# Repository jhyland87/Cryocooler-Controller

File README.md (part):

# ESP32-S3 Cryocooler Controller

Firmware for an ESP32-S3 DevKit that automates the cooldown sequence of a cryogenic cooler. The controller manages a compressor-driven cold stage through ten operational states — from a cold start at room temperature (~295 K) down to an operating setpoint of 78 K, with a graceful shutdown sequence — while enforcing thermal safety limits, detecting back-EMF current spikes, streaming live telemetry via Protobuf over WebSocket, and serving a real-time Preact dashboard over WiFi.

---

## Hardware

| Component | Part | Interface | Address / Pin | Purpose |
|-----------|------|-----------|---------------|---------|
| Microcontroller | ESP32-S3 DevKitC-1-N32R16V | — | — | Host MCU (32 MB flash, 16 MB PSRAM) |
| Cold-stage sensor | ADS1220 + PT1000 RTD | SPI mode 1 (main bus) | CS: decoder Y6 | Cold-stage temperature (4-wire, ratiometric) |
| Waveform generator | AD9837 DDS (AD9833 register set, 16 MHz clock) | SPI (main bus) | FSYNC (CS): decoder Y0 | 60 Hz sine wave for compressor |
| DAC | AD5453 14-bit multiplying | SPI mode 1 (main bus), write only | SYNC: decoder Y1 | Amplifier amplitude control |
| Power monitor | INA239 + 10 mΩ shunt | SPI mode 1 (main bus) | CS: decoder Y2, ALERT: expander GP6 | 12 V rail voltage, current and power |
| IMU | LSM6DSOX on the cryocooler: its own 18 x 18 mm board (`hardware/kicad/imu/`, not yet built) or the Adafruit breakout it replaces | SPI (main bus) via header J14 | CS: decoder Y7, INT1: GPIO 2, INT2: GPIO 39 | Vibration / overstroke detection |
| Fan / pump | 4-pin PWM through a BSS138DW dual driver | LEDC PWM + PCNT tach | PWM: GPIO 9 / 14, tach: GPIO 15 / 21 | Cooling fan + pump |
| Current sensor | ACS37800-015B5 (±15 A) behind an ISOW7741 isolator | SPI mode 3 (main bus, through two gates) | CS: decoder Y5 (rev 5; GPIO 17 on rev 4) | Amplifier AC current monitoring |
| Compressor relay | BSS138 → BSS84 high-side +12 V switch (130 mA max) | GPIO | GPIO 16 | Compressor relay on/off |
| Amplifier relay | BSS138 → BSS84 high-side switch | GPIO | GPIO 6 | Amplifier REM line on/off |
| Coolant flow sensor | Alphacool ES (Hall-effect) | GPIO | GPIO 18 | Coolant flow pulses |
| Coolant temperature | NTC thermistor | ADC | GPIO 4 | Coolant temp via voltage divider |
| Status LED | WS2812B-2020 RGB | GPIO | GPIO 38 | Fault / Ready indication |
| Expander | MCP23S08 | SPI (main bus) | CS: decoder Y3 | ±15 V flags, INA239 ALERT, ADT7320 INT and CT, 3 spare pins (rev 5; rev 4 also has the display backlight and touch IRQ) |
| Display (rev 5, schematic only) | Waveshare ESP32-S3-Touch-LCD-4.3B, off-board, with its own ESP32-S3 and firmware | CAN through a TCAN3414 (rev 6: one 6-pin JST PH header J15 inside the board, which also feeds it fused, unswitched 12 V) | CAN TX: GPIO 17, RX: GPIO 12 | Shows telemetry and sends commands. Its two digital outputs press the power button and RESET through J15 pins 5 and 6 (rev 5: header J21). Rev 6.1 adds J42 (JST PH: CAN_L, CAN_H, GND) to carry the bus on, and a 0 Ω link JP20 to take out the 120 Ω terminator when this board is mid-bus. No CAN firmware yet (the firmware still drives the rev 4 ST7789V + TSC2046) |
| Ambient temperature (rev 5, schematic only) | ADT7320 | SPI mode 3 (main bus) | CS: decoder Y8, INT / CT: expander GP2 / GP3 | Ambient temperature; replaces the reading the I2C fan controller gave |
| Power button | LTC2954 INT# / KILL# | GPIO | GPIO 1 / GPIO 10 | Button press ramps down, then cuts system power |
| General-purpose I/O | 2-pin headers J16-J18 and J20 (rev 4 also has J19 on GPIO 12) (signal, GND), each with an LED that follows the pin voltage | GPIO; ADC on IO5 / IO7 only | GPIO 5, 7, 11, 13 | Spare 3.3 V inputs or outputs (sensors, relay triggers, LEDs) |
| AUX header (rev 6) | 5-pin JST PH header J40 inside the board: 5 V, 3.3 V, GPIO11, GPIO13, GND; 100 Ω and an ESD clamp per line, pull-up footprints not fitted. Rev 6.1 adds a Qwiic / STEMMA QT header J41 on the same lines (1 GND, 2 3.3 V, 3 SDA = GPIO11, 4 SCL = GPIO13) | UART, I2C, 1-Wire, touch (T11, T13) or GPIO, chosen in firmware; ADC2 only with WiFi off | GPIO 11, 13 | Spare port for a later add-on. No firmware uses it yet |

**I2C:** none. Every peripheral is on SPI or a GPIO.

**Main SPI bus:** CLK → GPIO 42, MOSI → GPIO 41, MISO → GPIO 40. Devices: AD9837, AD5453, the LSM6DSOX (on a cable, header J14), INA239, ADS1220, MCP23S08, the ACS37800 and, up to rev 4, the display and its TSC2046 touch controller. Their chip selects come from the 74HC154 4-to-16 decoder (rev 5; rev 4 has an SN74LVC138A with eight outputs), driven from GPIO 3, 44, 45, 47 (through a 74LV1T34 buffer, because it is 1.8 V) and 8, with Y4 (rev 5) and Y9 to Y15 spare. The INA239, ADS1220 and AD5453 use SPI mode 1, and the INA239 and ADS1220 data outputs are high-impedance while CS is high. The ADS1220 DRDY pin is not wired to the MCU.

**ACS37800:** on the main SPI bus, with CS on GPIO 17 (a plain GPIO, not a decoder output) on rev 4, and on decoder output Y5 in the rev 5 schematic. The ACS37800 keeps MISO driven when CS is high, so two SN74LVC1G125 gates connect it only while CS is low: one passes SCK to the isolator, the other passes its MISO to the bus. See [`docs/acs37800.md`](docs/acs37800.md) for its SPI frame and bring-up gotchas.

**General-purpose I/O:** each of the five pins has 100 Ω in series, 200 kΩ to ground (the LED driver's divider) and an ESD clamp, and is 3.3 V only. GPIO 5 and 7 are ADC1 and can read analog with WiFi on; GPIO 11-13 are ADC2, so digital only. The firmware defines the pins (`AUX_IO*_PIN`) but does not use them yet.

**Fan and pump:** each PWM GPIO drives a BSS138 (GPIO high = PWM line low = 0 % drive), because the fan PWM line can reach 5.25 V. A 10 kΩ gate pull-up holds 0 % drive during boot. Each tach line has a 4.7 kΩ series resistor, a clamp on the GPIO side, and a 4.7 kΩ pull-up to 3.3 V. The 12 V pin of each header is fed through its own Bourns resettable fuse (F3 fan: MF-MSMF050/24X, 0.5 A hold; F4 pump: MF-MSMF250/16X, 2.5 A hold; nets `+12V_FAN`, `+12V_PUMP`), so a shorted cable trips it instead of F1. The parts are on the schematic and on the rev 7 board.

**INA239 ALERT:** drives its red LED only; it is not wired to the MCU, and the firmware does not read it.

### Circuit board

The 4-layer board (rev 7: 170 x 120 mm, for the Phoenix UCS 195-145 housing, routed, not bench tested; see [`hardware/HANDOFF_rev7.md`](hardware/HANDOFF_rev7.md)) is routed from the KiCad schematic in [`hardware/kicad/`](hardware/kicad/README.md). It has no section boxes on the silkscreen.

### System wiring

Every off-board connection except the GPIO headers J16 to J20. The order of the parts in the coolant loop is assumed. Redraw it with `python3 hardware/kicad/tools/gen_wiring_diagram.py`.

---

## Architecture

All subsystem modules follow a standardised lifecycle pattern built on a CRTP base class (`ModuleBase<T>`) with compile-time interface enforcement. Modules are registered in declarative arrays and initialised/serviced via generic helpers — adding a new module is a one-liner. See [`docs/modules.md`](docs/modules.md) for the full module authoring guide.

```mermaid
flowchart TD
    subgraph Persistent ["Persistent Modules (init once at startup)"]
        HW[hardware<br/>SPI buses]
        IMU[imu<br/>LSM6DSOX accelerometer]
        CMD[commands<br/>Serial console]
        DASH[dashboard<br/>WiFi + Preact SPA + WebSocket]
        TEL[telemetry<br/>Protobuf frame builder]
        SYS[sysinfo<br/>INA239 power monitor]
        OTA[ota<br/>HTTP firmware updates]
    end

    subgraph Control ["Control Modules (re-init on every Initialize state)"]
        COOL[cooling<br/>PWM fan + pump<br/>software LUT]
        CH[cold_head<br/>ADS1220 PT1000 RTD]
        AMP[amplifier<br/>AD9837 + AD5453 DAC + ACS37800]
        COMP[compressor<br/>relay GPIO]
        IND[indicator<br/>WS2812 RGB LED]
    end

    subgraph FSM ["Core Logic"]
        SM[state_machine<br/>Pure FSM — no hardware calls]
    end

    CH  -->|tempC, coolingRate, stalled| SM
    AMP -->|rmsV, overstroke| SM
    IMU -->|overstroke| SM
    SYS -->|sysVoltage| SM

    SM -->|dacTarget| AMP
    SM -->|compressorRelay, amplifierRelay| COMP
    SM -->|faultIndMode, readyIndMode| IND
    SM -->|Output| TEL

    TEL --> DASH
    TEL --> CMD

    classDef persistent fill:#dbeafe,stroke:#3b82f6,color:#1e3a5f
    classDef control    fill:#dcfce7,stroke:#16a34a,color:#14532d
    classDef fsm        fill:#fef3c7,stroke:#d97706,color:#78350f

    class HW,IMU,CMD,DASH,TEL,SYS,OTA persistent
    class COOL,CH,AMP,COMP,IND control
    class SM fsm

    style Persistent fill:#eff6ff,stroke:#93c5fd
    style Control    fill:#f0fdf4,stroke:#86efac
    style FSM        fill:#fffbeb,stroke:#fcd34d
```

---

## Module Reference

### hardware

Initialises the main SPI bus (`SPI.begin(...)`), which the ACS37800 shares.

---

### state_machine

The core of the controller. Ingests sensor readings every tick and outputs a complete set of actuator targets. Contains no hardware calls — pure logic, fully unit-testable on the host PC.

**States:**

| # | Name | Description | FAULT LED | READY LED | DAC |
|---|------|-------------|-----------|-----------|-----|
| -1 | Off | System powered down | Off | Off | 0 |
| 0 | Initialize | Power-up self-check | Solid Amber | Solid Amber | 0 |
| 1 | Idle | Warm standby | Solid Red | Off | 0 |
| 2 | CoarseCooldown | Cooling above 85 K | Flash Fast Red | Off | proportional to temp |
| 3 | FineCooldown | Cooling below 85 K | Flash Fast Red | Flash Slow Green | proportional to temp |
| 4 | Overshoot | Below setpoint, settling | Flash Fast Red | Flash Fast Green | 0 |
| 5 | Settle | In setpoint band; Normal relay | Flash Fast Red | Flash Fast Green | 0 |
| 6 | Baseline | Collecting pre-run baseline (5 min) | Off | Solid Green | 0 |
| 7 | Operating | Normal cryogenic operation | Off | Solid Green | 0 |
| 8 | Shutdown | Graceful shutdown; DAC ramps down | Off | Off | ramps → 0 |
| 9 | Delay | Timed hold; resumes at configured next state | Solid Amber | Solid Amber | 0 |
| 127 | Fault | Terminal fault state | Flash Fast Red | Off | 0 |

**Key configuration** (all in `config.h`):

| Constant | Default | Description |
|----------|---------|-------------|
| `SETPOINT_C` | -195.15 °C (78 K) | Target cold-stage temperature |
| `COARSE_FINE_THRESHOLD_C` | -188.15 °C (85 K) | Coarse/Fine transition boundary |
| `SETPOINT_TOLERANCE_C` | 3.0 °C | Band around setpoint for settle/overshoot logic |
| `SETTLE_DURATION_MS` | 60 000 ms | Time stable before advancing to Baseline |
| `BASELINE_DURATION_MS` | 300 000 ms | Baseline collection window |
| `SHUTDOWN_DURATION_MS` | 5 000 ms | Graceful shutdown ramp duration |
| `STALL_DETECT_WINDOW_MS` | 600 000 ms | Stall detection observation window |
| `STALL_MIN_DROP_C` | 2.0 °C | Minimum temp drop required in the window |
| `BACKOFF_MAX_COUNT` | 10 | Max overstroke events before TooManyBackoffs fault |

---

### cold_head

Reads the PT1000 RTD via the ADS1220 24-bit ADC over SPI (mode 1, chip select GPIO 44). The ADC is configured for 4-wire ratiometric measurement (gain 1, PGA bypassed, 20 SPS with simultaneous 50/60 Hz rejection) with 250 µA IDAC excitation and a 3854 Ω external reference resistor. Raw ADC counts are converted to resistance, then to temperature via the Callendar-Van Dusen equation (above 0 °C) and AN709 polynomial (below 0 °C).

Uses a non-blocking two-phase state machine: start single-shot conversion → wait out the 50 ms conversion time (DRDY is not wired) → read the 24-bit result. Maintains a ring buffer of `TEMP_HISTORY_SIZE` timestamped samples for cooling-rate calculation (°C/min), stall detection, and cooldown progress (0–100 %).

The temperature is reported (telemetry, dashboard, run history, display) only once it has settled: `COLD_HEAD_STABLE_READINGS` consecutive readings, each within `COLD_HEAD_STABLE_BAND_C` of the one before (about 2 s after boot, and again after any sensor fault). Until then it is sent as "no reading" instead of 0. This gate is for reporting only; the state machine's sensor-fault check is unchanged.

| Function | Returns |
|----------|---------|
| `getLastTempK()` | Cold-stage temperature in Kelvin |
| `getLastTempC()` | Cold-stage temperature in Celsius |
| `getCoolingRateCPerMin()` | °C/min, positive = cooling |
| `isStalled()` | True if stall threshold exceeded |

---

### amplifier

Drives the AD9837 DDS (60 Hz sine wave, through the MD_AD9833 library set to a 16 MHz clock), the AD5453 14-bit multiplying SPI DAC (amplifier amplitude), the amplifier relay (GPIO 6) and the ACS37800 current sensor. Provides two ramp modes:

- `rampToVoltage(target)` — smooth ramp at ±`DAC_MAX_STEP_PER_INTERVAL` per tick
- `rampTowardShutdown(target)` — fast ramp at ±`DAC_SHUTDOWN_STEP_PER_INTERVAL` per tick

**Overstroke (back-EMF) detection:** A slow-tracking EMA forms the baseline. A reading exceeding `baseline + OVERSTROKE_CURRENT_THRESHOLD_A` fires `hasOverstroke()`, subject to `OVERSTROKE_DEBOUNCE_MS`. The EMA is primed for `OVERSTROKE_PRIME_READINGS` ticks on startup.

---

### imu

Drives the LSM6DSOX 6-DOF IMU over SPI (CS GPIO 1) in FIFO mode at 833 Hz. The sensor is mounted on the cryocooler, so it sees the cooler body's vibration. It is cabled to header J14: the IMU board (`hardware/kicad/imu/`, not yet built) or, until then, the Adafruit breakout (product 4438); pinouts are in `hardware/kicad/README.md`. The SPI clock is `LSM6DSOX_SPI_FREQUENCY_HZ`. A missing cable is non-fatal: the module reports unavailable. On `init()` the module sets `I2C_disable` in CTRL4_C (13h) right after the driver's `begin_SPI()`, so the IMU's I²C block ignores traffic for the other devices on the shared SCK/MOSI lines (DS12814 §5.1.1; the driver only disables I3C). The sensor is then configured and a one-time blocking calibration collects samples to compute per-axis offsets (gravity is removed from the Z offset).

Each `service()` call applies calibration offsets, runs a first-order low-pass filter, and computes roll/pitch from filtered acceleration. Motion / overstroke is flagged when acceleration magnitude deviates from 9.81 m/s² by more than `ACCEL_THRESHOLD_MPS2`; it clears after `MOTION_TIMEOUT_MS` of stillness.

A periodic FFT (`calculateFrequency()`) detects the compressor vibration frequency in the 45–75 Hz band using 256 samples at 833 Hz, with Hann windowing and quadratic peak interpolation.

| Function | Returns |
|----------|---------|
| `isInitialized()` | True if sensor was found and configured |
| `hasOverstroke()` | True while motion/overstroke is active |
| `getRoll()` / `getPitch()` | Orientation angles in degrees |
| `getAccelMag()` | Calibrated acceleration magnitude (m/s²) |
| `getFrequencyHz()` | Detected compressor frequency (Hz), or NAN |
| `getTemperature()` | IMU die temperature (°C); mounted on the cooler, this is the cooler-body temperature and also feeds the "ambient" value |

---

### sysinfo

Reads the 12 V rail voltage, current and power from the INA239 power monitor over SPI (10 mΩ shunt, 10 A calibration; GPIO 3 chip select) and exposes `getVoltage()`, `getCurrent()` and `getPower()`. SPI has no ACK, so each tick first reads the INA239 manufacturer and device ID registers; after 3 consecutive failures (for example when 12 V drops) the module disables itself until `reinit`. It also tracks CPU load, heap and PSRAM.

---

### cooling

Controls the cooling fan and pump directly from the ESP32: LEDC generates 25 kHz PWM and PCNT counts the tach pulses. Also samples the Alphacool ES flow sensor and NTC coolant temperature.

**Software LUT:** Each channel has an independently-configured temperature-to-duty lookup table with hysteresis, evaluated once per second from coolant temperature. Entries are sorted ascending by temperature; the evaluator only writes to the chip when the active row changes.

**Fault detection:** A channel with drive applied and no tach pulses for `COOLING_TACH_STALL_MS` raises `hasFanFault()`. It is reported in telemetry and logs and does not fault the state machine.

**Pump normalisation:** User-facing pump speeds are 0–100 % normalised, mapped to 0–`COOLING_PUMP_MAX_DUTY_PCT` (raw 0–255) at the hardware boundary. The pump stalls above ~16 % effective duty (~4400 RPM).

**Tracking monitors:** Score-based monitors for fan duty, coolant temperature, and flow rate detect sustained deviations from expected values.

| Function | Returns |
|----------|---------|
| `getCoolantTemperature()` | Coolant temperature in °C |
| `getCoolantFlowRate()` | Coolant flow rate in L/min |
| `getFanSpeed()` | Fan duty (0–255) |
| `getFanRPM()` | Fan tachometer RPM |
| `getPumpSpeed()` | Pump speed (normalised 0–100 %) |
| `getPumpRPM()` | Pump tachometer RPM |
| `hasFanFault()` | True while a driven channel has no tach pulses |
| `getFanFaultDurationMs()` | Duration of current fault episode |

---

### compressor

Manages the compressor relay (GPIO 16 → high-side +12 V switch) with timed-run support. `compressor start <duration>` energises the relay for a specified duration (e.g. `1h30m`, `45s`), clamped to `COMPRESSOR_MAX_RUN_MS`. Can be disabled at compile time with `ENABLE_COMPRESSOR false`.

---

### indicator

Drives the on-board WS2812 RGB LED (GPIO 38) according to the state machine's requested `Mode`. All flash timing is non-blocking — `update(nowMs)` is called every loop iteration.

| Mode | Colour | Rate |
|------|--------|------|
| `SolidRed` | Red | — |
| `SolidGreen` | Green | — |
| `SolidAmber` | Amber | — |
| `FlashFastRed` | Red | 2 Hz |
| `FlashSlowGreen` | Green | 1 Hz |
| `FlashFastGreen` | Green | 2 Hz |

---

### dashboard

Connects to WiFi and serves a Preact single-page application with real-time telemetry:

- **HTTP** (port 80): serves the embedded SPA (`index.html`, `app.js`, `style.css`) and a JSON telemetry endpoint at `GET /api/telemetry`
- **WebSocket** (`ws://<hostname>/ws` on port 80): streams Protobuf-encoded telemetry frames at 1 Hz
- **Network panel**: hostname, IP address, joined WiFi network and signal strength, from the `network.*` telemetry group
- **mDNS**: `cryocooler.local` by default. Change `HOSTNAME` in `include/config/config.h`; the firmware and the dashboard build both read it, so rebuild both (a full `pio run`).

The dashboard frontend uses Preact + MUI + Vite and is bundled into firmware flash at build time via `scripts/embed_web.py`. WiFi credentials are set from the serial console (`wifi set`) and saved in NVS flash; see [WiFi credentials](#wifi-credentials).

---

### ota

HTTP OTA firmware update endpoint. `GET /ota` serves an upload form; `POST /ota` flashes new firmware. Enabled with `ENABLE_OTA true` in `config.h`. Every `/ota` request needs the OTA login; see [Passwords](#passwords).

---

### commands

Non-blocking USB serial command handler. `service()` accumulates characters and dispatches completed lines. The same `processLine()` function is used by the TCP server and by unit tests with a stub `Print`.

| Command | Action |
|---------|--------|
| `start` | Begin cooldown (from Off or Idle) |
| `stop` | Abort and return to Idle |
| `off` | Power off the system entirely |
| `reboot` | Reboot the MCU |
| `status` | Print current state and running flag |
| `summary` | Full snapshot of all sensor and actuator values |
| `fsm state` | Print current FSM state with time-in-state |
| `fsm history` | Print recent FSM state transitions |
| `fault clear` | Clear an active fault and return to Idle |
| `fault push` | Push a fault record |
| `fault history` | Print fault log with reason and clear method |
| `board` | Print compile-time board/platform info |
| `reinit` | Re-initialise all or named modules |
| `wifi status` | Print WiFi on/off state, saved settings, link, signal, TX power and last disconnect reason |
| `wifi retry` | Start a new WiFi connection attempt now |
| `wifi on` / `wifi off` | Turn WiFi on or off until reboot |
| `wifi onboot <on\|off>` | Save whether WiFi starts at boot (also `true`/`false`/`1`/`0`); no argument prints the setting |
| `wifi scan` | List visible networks with RSSI, channel and security (serial port only) |
| `wifi set <ssid>` | Save a network; the passphrase is asked for on the next line |
| `wifi forget` | Erase the saved network and disconnect |
| `dashboard password` | Set or remove the dashboard password; asked for on the next line (`none` removes it) |
| `ota password` | Set the OTA update password; asked for on the next line (`default` restores the default) |
| `dashboard logout` | End every dashboard login, including remembered ones |
| `password status` | Show whether each password is set (never prints them) |
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
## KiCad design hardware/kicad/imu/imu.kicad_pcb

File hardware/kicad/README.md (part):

# Cryocooler controller — KiCad schematic

KiCad 10 hierarchical schematic for the ESP32-S3 cryocooler controller. Open
`cryocooler.kicad_pro`. A PDF export is in `cryocooler-schematic.pdf`. The 4-layer board is `cryocooler.kicad_pcb` (see [PCB layout](#pcb-layout)).

GPIO assignments follow [`include/config/pin_config.h`](../../include/config/pin_config.h).
The top-level README hardware table was brought in line with these sheets and the firmware
on 2026-10-14; if the two ever disagree, the schematic and `pin_config.h` win.

## Sheets

| Sheet | Contents |
|---|---|
| `cryocooler.kicad_sch` (root) | ESP32-S3-WROOM-2-N32R16V, EN/BOOT, USB-C (GCT USB4205-GF-A, flag type) + ESD |
| `power_input` | 12 V DC jack (5.5 x 2.1 mm), 5 A fuse, SMBJ16A TVS, bulk caps Rev 5 (2026-11-16): sized for 10 A. J2 is a Molex Mini-Fit Jr 2 x 2 pinned as the ATX 12 V (CPU) connector (1, 2 ground; 3, 4 +12 V) and F1 is 10 A. |
| `power_button` | LTC2954CDDB-2 (INT# to GPIO1), AONR21307 high-side P-FET with slow-start gate network and 15 V clamp, KILL# bias, red standby LED through 13 kΩ and one BSS138, TPD1E05U06 on the button line `PWR_BTN` (the J7 panel header went in rev 4). Rev 5: `PWR_BTN` is a global label, so the display's digital output on the `display` sheet (J21) presses the same line as SW3 Rev 5: optional auto power-on (JP, 2.2 µF and a diode on `PWR_BTN`), jumper not fitted, not bench tested. |
| `rails_logic` | AP63205 buck with SRP4020TA-4R7M (12→5 V); TPS2116 selects +5V or USB VBUS into +5V_OR, priority to the 12 V side → TPS62822 buck with SRP4020TA-R47M (→3.3 V) |
| `rails_15v` | ADP5071ACPZ dual converter at 1.2 MHz with SRP7050TA-3R3M and -6R8M (rev 1 values) → one LT3097 dual LDO (±14.7 V, 147 kΩ SET resistors); the LT3097 PGP / PGN go to the `power_good` sheet Rev 5 (2026-11-16): the LT3097 (no stock) is replaced by an LT3045 (MSOP-12, U21) and an LT3094 (DFN-12, U22) with the same SET, PGFB and output parts. |
| `ldo_15v` ("Regulators +-15V") | The LT3045 (+15 V) and LT3094 (-15 V) post-regulators with their SET, PGFB and output parts. Split off `rails_15v` in the schematic redraw (that sheet was over 30 parts); the circuit and the references are unchanged. Its block carries the PGP_15V / PGN_15V pins. |
| `power_good` | One node and green LED per LT3097 PG pin (with a 470 k / 470 k guard and BSS138W so a missing -15 V pulls `PGN_15V` low), a BAT54AW AND of the two nodes into `PG_15V`, and the 3.3 V flag `PG_15V_N` on GPIO43 (low = both ±15 V rails good); both flags are also read by the MCP23S08 |
| `signal_gen` | ECS-2520MV 16 MHz oscillator, AD9837 (LFCSP-10), OPA2991 dual U5 (A: gain 16.3; B: AD5453 output stage, 22 pF C1), R39 + MMBZ9V1 clamp into AD5453 VREF, AD5453 (decoder Y1); all digital parts on `+3V3_SG` |
| `amp_control` | GPIO6 → BSS138 → BSS84 high-side 12 V to amplifier REM, red/green LED; a second BSS138 (Q9) in series with the level shifter's source is gated by `PG_15V`, so REM cannot turn on unless both ±15 V rails are good |
| `amp_current` | ACS37800-015B5 (SPI, ±15 A at 5 V) + ISOW7741 (isolated 5 V and SPI in one part) with FB1 / FB2, 4×1 MΩ + 4.02 kΩ divider, TE 2305908-2 SMT pluggable header J11, TE 643228-1 through-hole header J12. Rev 4: on the shared SPI bus through two SN74LVC1G125 gates enabled by `ACS_CS` (U41 passes SCK in, U42 passes MISO out), with 10 kΩ pull-ups on the gated SCK and on `ACS_CS` Rev 5 (2026-11-15): the ISOW7741 (no stock) is replaced by an ISOW7841AQDWERQ1 on `+3V3_ISO` (40 mA at 5 V out); FB1 / FB2 and the EN/FLT pull-up are gone. |
| `system_current` | INA239 (SPI mode 1, decoder Y2) + 15 mΩ shunt in the switched 12 V rail, 49.9 Ω / 470 nF input filter, ALERT to expander GP6, ALERT and 3V3 power LEDs Rev 5: the shunt is a 4-terminal part whose sense pads feed the filter, and VBUS sits on `+12V` directly. Later (2026-11-16): the shunt is a 10 mΩ Vishay WSK2512 (16.4 A full scale). |
| `gpio_expander` ("GPIO Expander") | MCP23S08 QFN-20 on the shared SPI bus (mode 0, decoder Y3), on unswitched `+3V3`: GP0-1 power-good flags, GP6 INA239 ALERT, GP2/GP3 ADT7320 INT/CT, GP4, GP5 and GP7 spare (rev 5; GP4 was the display backlight enable and GP7 the touch IRQ); RESET tied to +3V3, A0/A1 and exposed pad to GND, INT to a test point Rev 5 universal I/O: GP4 is `IO_EXP_INT_N` and GP5 `IO_ADC_DRDY_N`; only GP7 is spare. |
| `cooling` ("Water Cooling") | Fan and pump: LEDC PWM through the two halves of one BSS138DW (Q61) as open-drain drivers (gates held on by 10 kΩ to `+3V3`, so 0% drive at reset), tach through 4.7 kΩ to PCNT; Alphacool ES flow tach and NTC; connector-side pull-ups sit on the switched `+3V3_COOL` rail. 2026-11-23: the +12 V pin of J3 and J4 is fed through resettable fuses F3 (MF-MSMF050/24X, net `+12V_FAN`) and F4 (MF-MSMF250/16X, net `+12V_PUMP`), each with its 22 uF cap on the header side; on the rev 7 board both stand on the back above J4, with the pump fuse's pad 1 straight to J4 pin 2 and the fan fuse's through two vias to J3 pin 2. Rev 4: XKB X2510WRS headers (J5 is a 4-pin part with pin 4 unused), 4.7 kΩ and 10 kΩ resistors in arrays RN1 / RN2 |
| `cold_head` ("Cold Head Temp") | ADS1220 (SPI mode 1, CS on GPIO44), 4-wire PT1000, 3.9 kΩ Rref, DRDY pull-up + test point; powered from the switched `+3V3_CH` rail |
| `imu` | J14, a Molex Micro-Lock Plus 2x4 header (505448-0891, 1.25 mm, right angle, positive lock) for the off-board Adafruit LSM6DSOX module: SPI bus, CS, INT1/INT2, +3V3, GND; one NUF6401MN six-channel filter (100 Ω series, 17 pF and ESD clamp each side) |
| `compressor_relay` | GPIO16 → BSS138 → BSS84 high-side +12 V switch, flyback diode, red/green state LED, 2-pin right-angle XKB X2510WRS-02 output |
| `indicators` | WS2812B-2020 status LED behind a 74AHCT1G125 level shifter |
| `debug` | Test points on rails, grounds and control lines; LEDs on +5V and ISO 5V |
| `supply_switches` | 5 Keystone 5110 0603 zero-ohm jumpers JP1-JP5, one per section, in series with that section's supply (see "Supply jumpers" below); FB3 ahead of JP5 Rev 5: JP3 now feeds `+3V3_ISO`, and JP6 with FB4 feeds `+5V_IO` from `+5V` (universal I/O ADC, range switches and sensor excitation). |
| `display` | Rev 5: link to the off-board Waveshare ESP32-S3-Touch-LCD-4.3B, which runs its own firmware. TCAN3414 CAN transceiver (U52, `CAN_TX` GPIO17 with a 10 kΩ pull-up, `CAN_RX` GPIO12, 120 Ω termination R516) to J15 (X2510WRS-04: 1 GND, 2 unswitched 12 V `VIN`, 3 CAN_H, 4 CAN_L). J21 (X2510WRS-04: 1 GND, 2 power button, 3 reset, 4 unused) lets the display's two open-collector outputs press the global `PWR_BTN` like SW3 and pull `ESP_EN` low like the RESET button, each through 100 Ω with a TPD1E05U06 clamp. Rev 4 and earlier: FH12-14S FPC to the Phoenix 2.4" ST7789V display with a TSC2046 touch controller Later on 2026-11-15: J15 and J21 became one 6-pin connector J15 (1 GND, 2 fused 12 V, 3 CAN_H, 4 CAN_L, 5 power button, 6 reset), with a 0.5 A resettable fuse F2 and an ESD2CAN24 clamp; since 2026-11-16 the cable ends in two XKB headers back to back, as XKB makes no 6-pin part: J15 (X2510WRS-04: 1 CAN_H, 2 CAN_L, 3 power button, 4 reset) and J21 (X2510WRS-02: 1 GND, 2 fused 12 V). Rev 6 (2026-11-18): one 6-pin top-entry JST PH header J15 again (B6B-PH-SM4-TB: 1 GND, 2 fused 12 V, 3 CAN_H, 4 CAN_L, 5 power button, 6 reset); J21 is gone. |
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
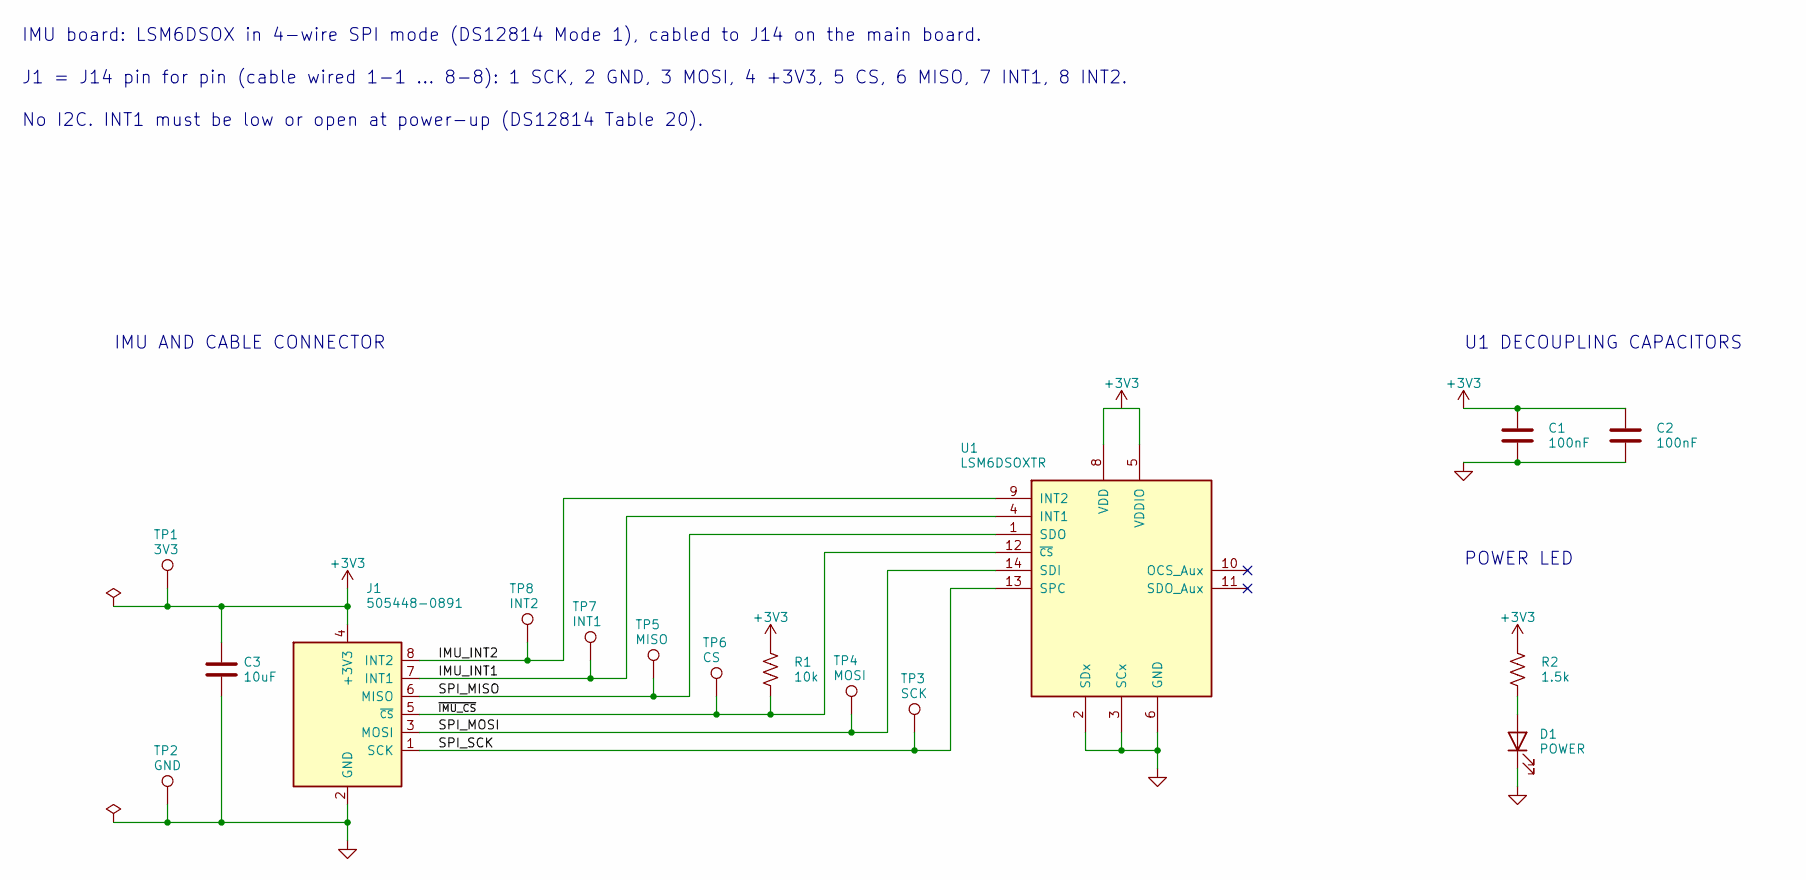
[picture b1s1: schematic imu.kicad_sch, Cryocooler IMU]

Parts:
C1, C2: 100nF; C_0402_1005Metric
C3: 10uF; C_0805_2012Metric
D1: POWER; LED_0402_1005Metric
J1: 505448-0891; Molex_Micro-Lock_Plus_505448-0891_2x04_P1.25mm_Horizontal
R1: 10k; R_0402_1005Metric
R2: 1.5k; R_0402_1005Metric
TP1: 3V3; TestPoint_Pad_D1.0mm
TP2: GND; TestPoint_Pad_D1.0mm
TP3: SCK; TestPoint_Pad_D1.0mm
TP4: MOSI; TestPoint_Pad_D1.0mm
TP5: MISO; TestPoint_Pad_D1.0mm
TP6: CS; TestPoint_Pad_D1.0mm
TP7: INT1; TestPoint_Pad_D1.0mm
TP8: INT2; TestPoint_Pad_D1.0mm
U1: LSM6DSOXTR; LGA-14_3x2.5mm_P0.5mm_LayoutBorder3x4y

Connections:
+3V3: C1.1, C2.1, C3.1, J1.4 (+3V3), R1.1, R2.1, TP1.1, U1.5 (VDDIO), U1.8 (VDD)
/IMU_INT1: J1.7 (INT1), TP7.1, U1.4 (INT1)
/IMU_INT2: J1.8 (INT2), TP8.1, U1.9 (INT2)
/SPI_MISO: J1.6 (MISO), TP5.1, U1.1 (SDO)
/SPI_MOSI: J1.3 (MOSI), TP4.1, U1.14 (SDI)
/SPI_SCK: J1.1 (SCK), TP3.1, U1.13 (SPC)
/~IMU_CS: J1.5 (~CS), R1.2, TP6.1, U1.12 (~CS)
GND: C1.2, C2.2, C3.2, D1.1 (K), J1.2 (GND), TP2.1, U1.2 (SDx), U1.3 (SCx), U1.6 (GND), U1.7 (GND)
unnamed: D1.2 (A), R2.2

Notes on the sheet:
U1 DECOUPLING CAPACITORS
J1 = J14 pin for pin (cable wired 1-1 ... 8-8): 1 SCK, 2 GND, 3 MOSI, 4 +3V3, 5 CS, 6 MISO, 7 INT1, 8 INT2.
IMU AND CABLE CONNECTOR
No I2C. INT1 must be low or open at power-up (DS12814 Table 20).
POWER LED
IMU board: LSM6DSOX in 4-wire SPI mode (DS12814 Mode 1), cabled to J14 on the main board.

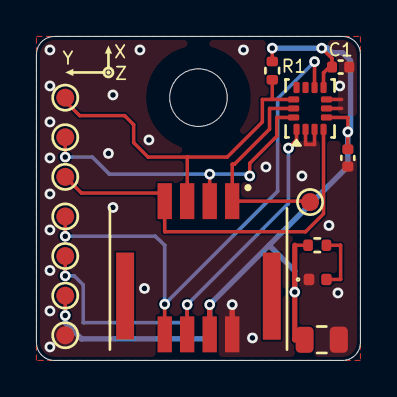
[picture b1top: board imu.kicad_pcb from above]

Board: 2 copper layers, 18.0 x 18.0 mm, 16 parts (0 on the bottom side), 9 nets.

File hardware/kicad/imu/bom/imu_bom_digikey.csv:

Quantity,Manufacturer Part Number,Manufacturer,Description,Customer Reference,Value,Package,MPN basis,Notes
2,CL05B104KB54PNC,Samsung Electro-Mechanics,CAP CER 0.1UF 50V X7R 0402,C1 C2,100nF,C_0402_1005Metric,suggested,
1,CL21A106KACLRNC,Samsung Electro-Mechanics,CAP CER 10UF 25V X5R 0805,C3,10uF,C_0805_2012Metric,ordered,substitute for CL21A106KAYNNNE
1,APHHS1005CGCK,Kingbright,LED GREEN (570 NM) CLEAR 0402 SMD,D1,green,LED_0402_1005Metric,suggested,"indicators sized for ~1 mA (1.5k on 3.3 V, 3.3k on 5 V, 13k on 15 V); AlGaInP green, Vf 2.1 V typ"
1,505448-0891,Molex,CONN HEADER R/A 8POS 1.25MM DUAL ROW SMD,J1,505448-0891,Molex_Micro-Lock_Plus_505448-0891_2x04_P1.25mm_Horizontal,design,"J14 IMU cable; Micro-Lock Plus, positive lock, 30 mating cycles; mates with a 505432 series 8-circuit dual-row housing"
1,RC0402FR-0710KL,Yageo,RES 10K OHM 1% 1/16W 0402,R1,10k,R_0402_1005Metric,suggested,
1,RC0402FR-071K5L,Yageo,RES 1.5K OHM 1% 1/16W 0402,R2,1.5k,R_0402_1005Metric,suggested,
1,LSM6DSOXTR,STMicroelectronics,IMU ACCEL/GYRO I2C/SPI 14LGA,U1,LSM6DSOXTR,LGA-14_3x2.5mm_P0.5mm_LayoutBorder3x4y,design,"IMU board (imu/): SPI mode, datasheet DS12814"

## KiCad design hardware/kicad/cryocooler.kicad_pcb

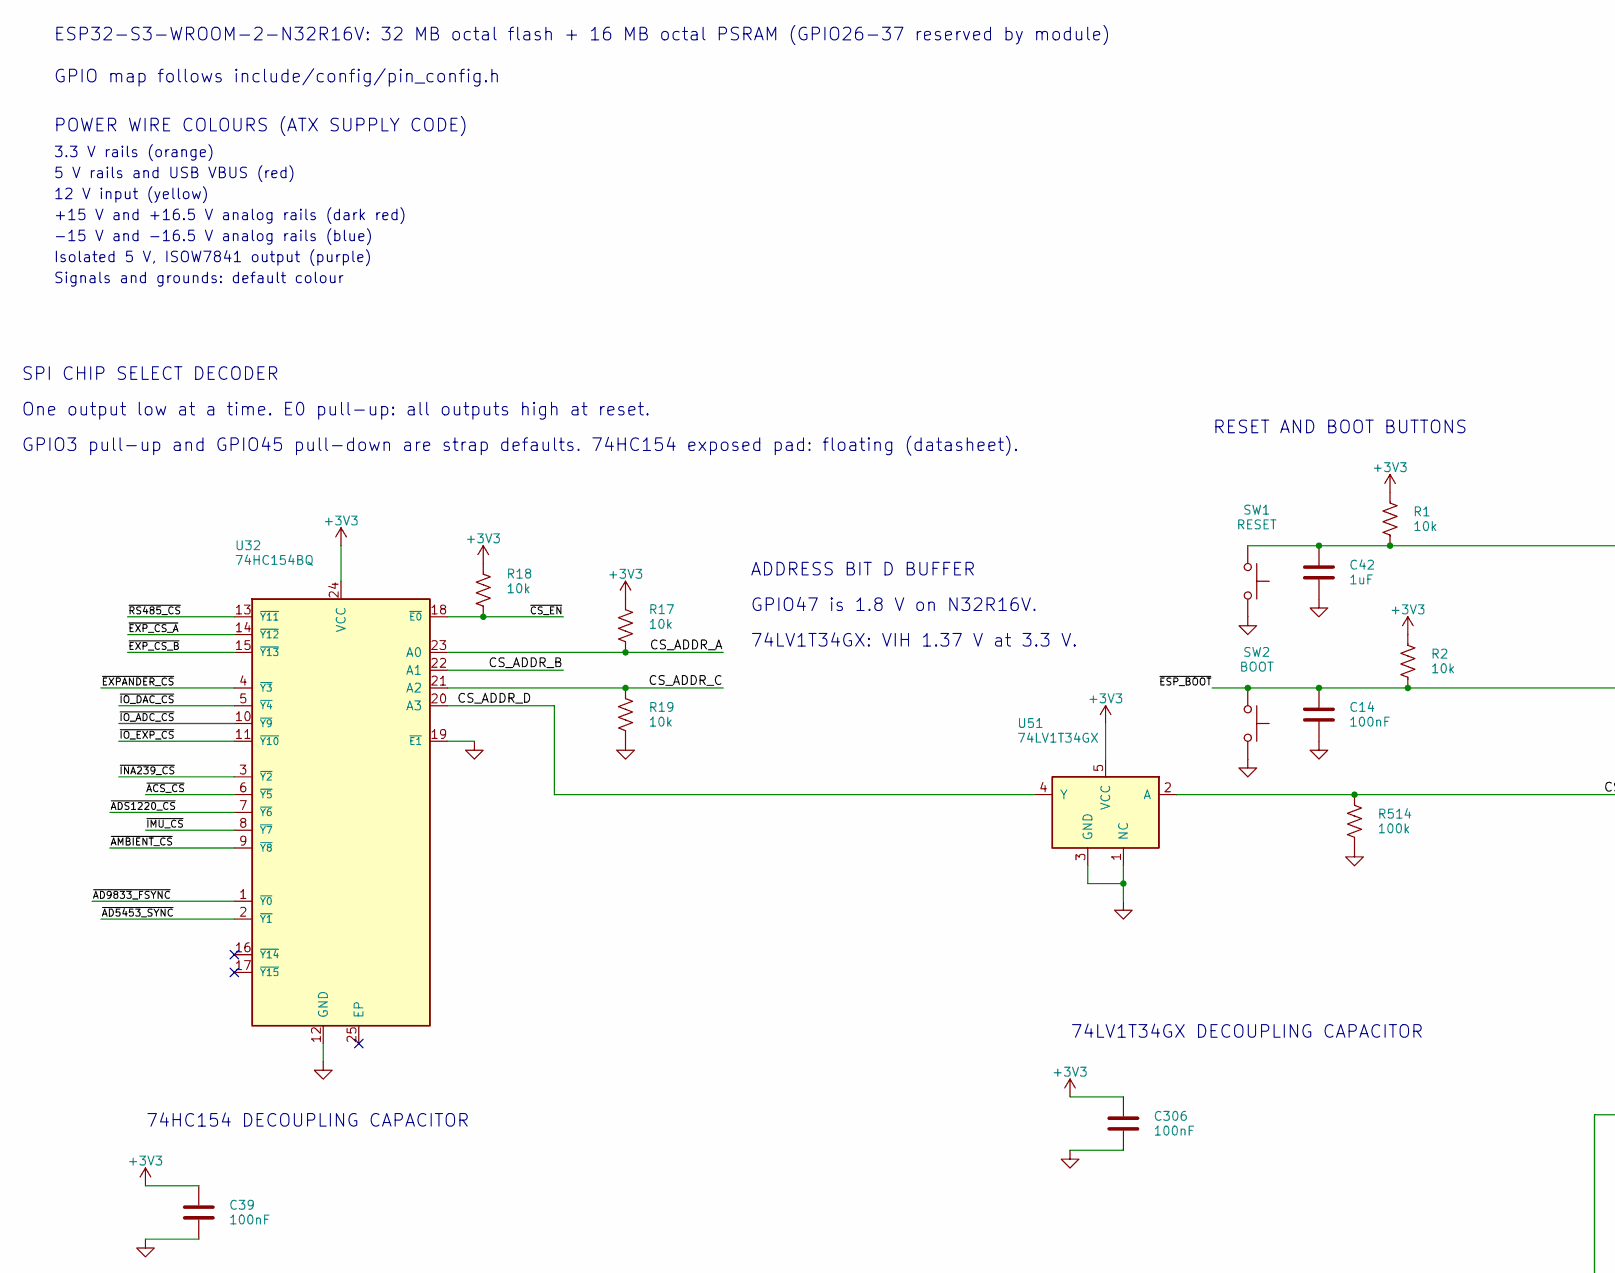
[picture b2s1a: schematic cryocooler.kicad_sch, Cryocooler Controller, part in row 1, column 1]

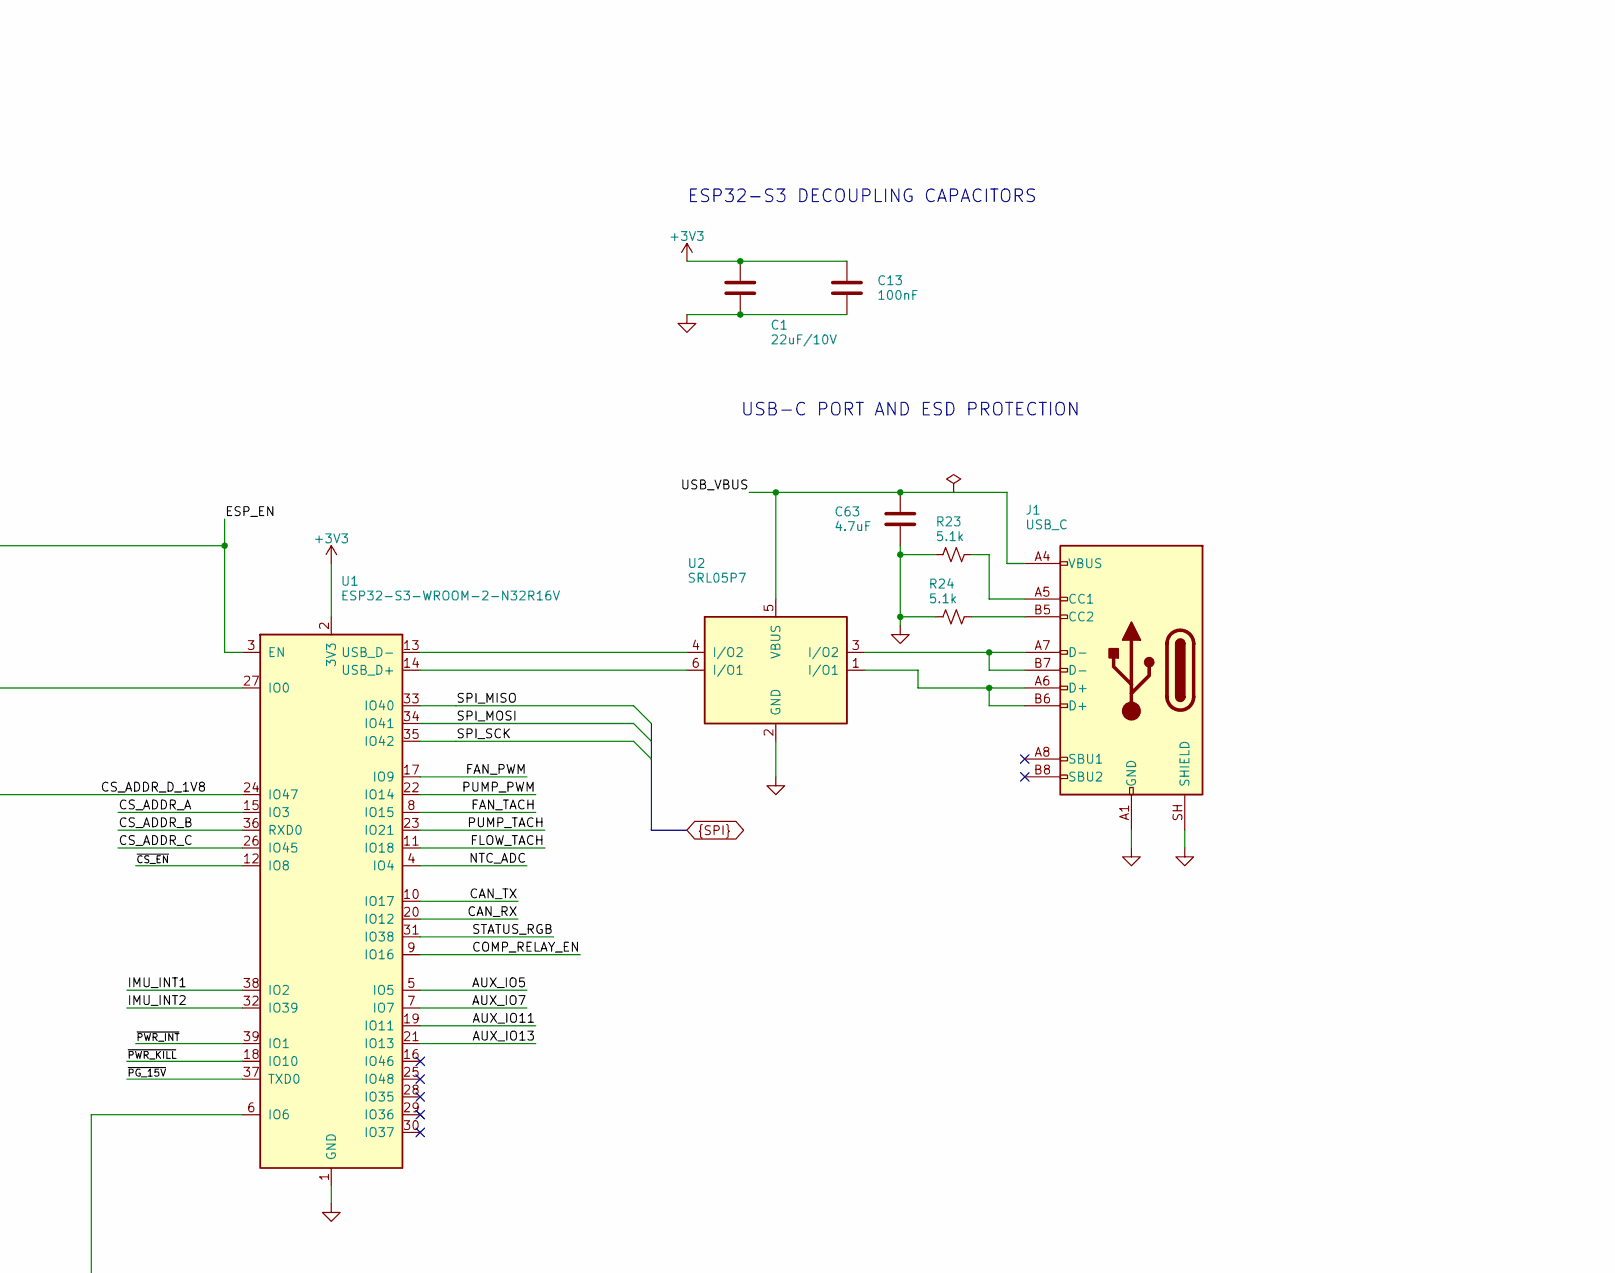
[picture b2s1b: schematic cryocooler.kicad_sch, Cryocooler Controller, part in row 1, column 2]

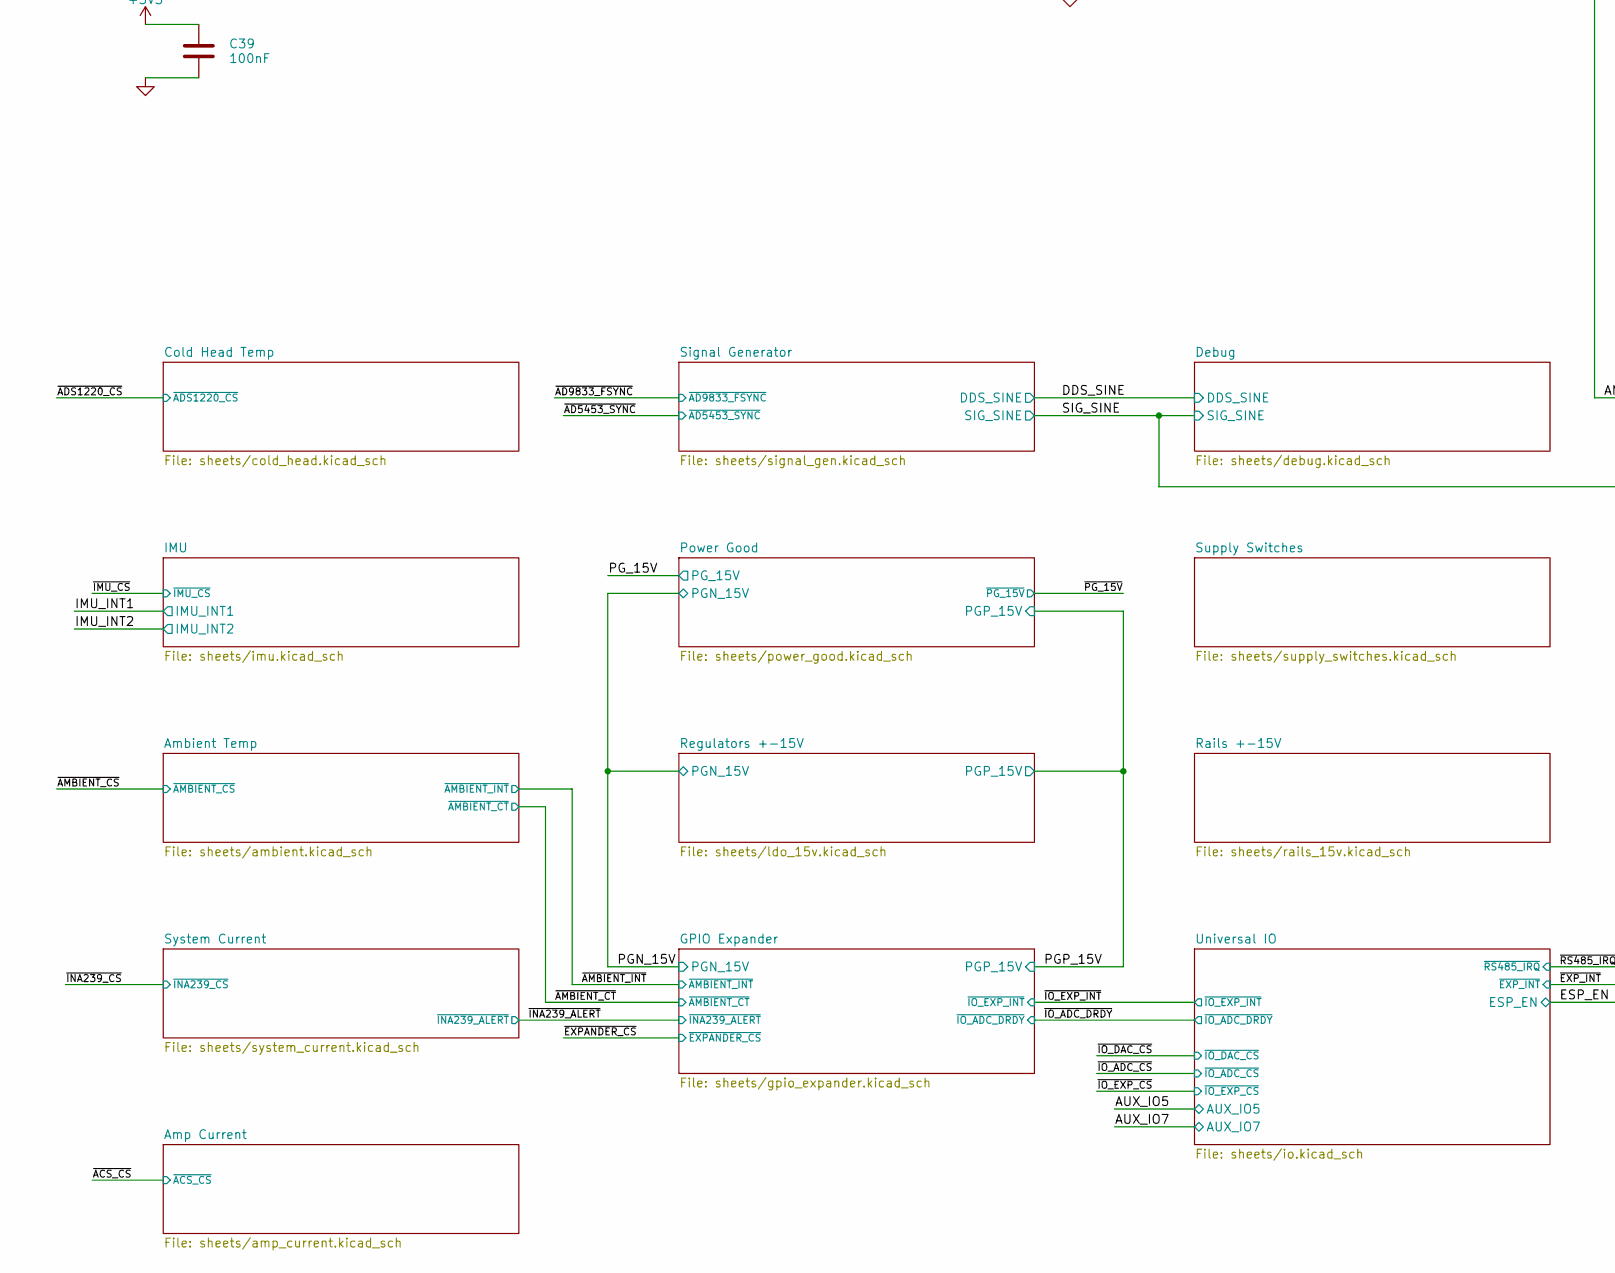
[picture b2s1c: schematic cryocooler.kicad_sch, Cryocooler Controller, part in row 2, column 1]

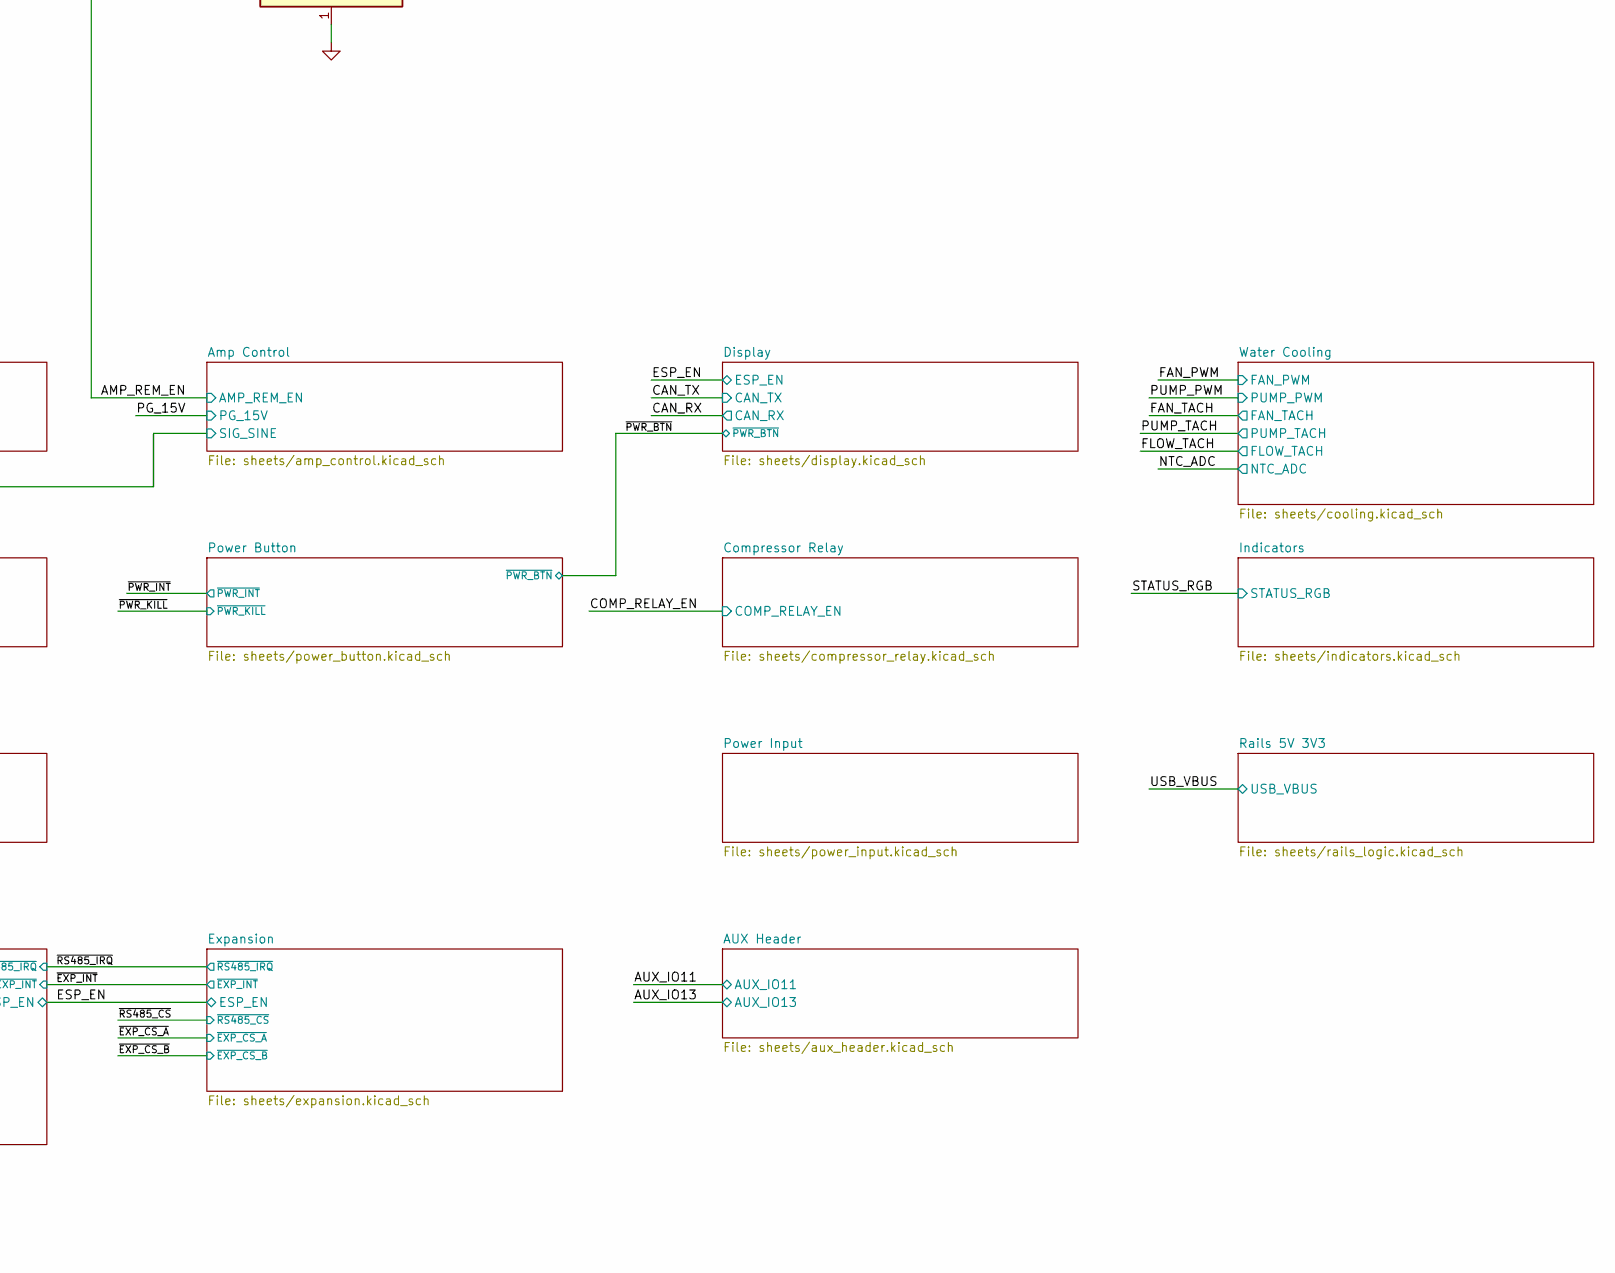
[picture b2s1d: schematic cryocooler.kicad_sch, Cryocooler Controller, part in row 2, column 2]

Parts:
C1: 22uF/10V; C_1206_3216Metric
C13, C14, C39, C306: 100nF; C_0402_1005Metric
C42: 1uF; C_0603_1608Metric
C63: 4.7uF; C_0805_2012Metric
J1: USB_C; USB_C_Receptacle_GCT_USB4205-GF-A_16P_Flag
R1, R2, R17, R18, R19: 10k; R_0402_1005Metric
R23, R24: 5.1k; R_0402_1005Metric
R514: 100k; R_0402_1005Metric
SW1: RESET; SW_Panasonic_EVP-AA
SW2: BOOT; SW_Panasonic_EVP-AA
U1: ESP32-S3-WROOM-2-N32R16V; ESP32-S3-WROOM-2
U2: SRL05P7; MCC_DFN1510-6_1.5x1.0mm_P0.5mm
U32: 74HC154BQ; Nexperia_SOT815-1_DHVQFN-24-1EP_3.5x5.5mm_P0.5mm
U51: 74LV1T34GX; Nexperia_X2SON-5_SOT1226-3_0.8x0.8mm_P0.5mm

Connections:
+3V3: C1.1, C13.1, C39.1, C306.1, R1.1, R2.1, R17.1, R18.1, U1.2 (3V3), U32.24 (VCC), U51.5 (VCC); also elsewhere on the board
/AMP_REM_EN: U1.6 (IO6); also elsewhere on the board
/AUX_IO5: U1.5 (IO5); also elsewhere on the board
/AUX_IO7: U1.7 (IO7); also elsewhere on the board
/AUX_IO11: U1.19 (IO11); also elsewhere on the board
/AUX_IO13: U1.21 (IO13); also elsewhere on the board
/CAN_RX: U1.20 (IO12); also elsewhere on the board
/CAN_TX: U1.10 (IO17); also elsewhere on the board
/COMP_RELAY_EN: U1.9 (IO16); also elsewhere on the board
/CS_ADDR_A: R17.2, U1.15 (IO3), U32.23 (A0)
/CS_ADDR_B: U1.36 (RXD0), U32.22 (A1)
/CS_ADDR_C: R19.2, U1.26 (IO45), U32.21 (A2)
/CS_ADDR_D: U32.20 (A3), U51.4 (Y)
/CS_ADDR_D_1V8: R514.1, U1.24 (IO47), U51.2 (A)
/ESP_EN: C42.1, R1.2, SW1.1, U1.3 (EN); also elsewhere on the board
/FAN_PWM: U1.17 (IO9); also elsewhere on the board
/FAN_TACH: U1.8 (IO15); also elsewhere on the board
/FLOW_TACH: U1.11 (IO18); also elsewhere on the board
/IMU_INT1: U1.38 (IO2); also elsewhere on the board
/IMU_INT2: U1.32 (IO39); also elsewhere on the board
/NTC_ADC: U1.4 (IO4); also elsewhere on the board
/PUMP_PWM: U1.22 (IO14); also elsewhere on the board
/PUMP_TACH: U1.23 (IO21); also elsewhere on the board
/STATUS_RGB: U1.31 (IO38); also elsewhere on the board
/USB_VBUS: C63.1, J1.A4 (VBUS), J1.A9 (VBUS), J1.B4 (VBUS), J1.B9 (VBUS), U2.5 (VBUS); also elsewhere on the board
/~ACS_CS: U32.6 (~Y5); also elsewhere on the board
/~AD5453_SYNC: U32.2 (~Y1); also elsewhere on the board
/~AD9833_FSYNC: U32.1 (~Y0); also elsewhere on the board
/~ADS1220_CS: U32.7 (~Y6); also elsewhere on the board
/~AMBIENT_CS: U32.9 (~Y8); also elsewhere on the board
/~CS_EN: R18.2, U1.12 (IO8), U32.18 (~E0)
/~ESP_BOOT: C14.1, R2.2, SW2.1, U1.27 (IO0)
/~EXPANDER_CS: U32.4 (~Y3); also elsewhere on the board
/~EXP_CS_A: U32.14 (~Y12); also elsewhere on the board
/~EXP_CS_B: U32.15 (~Y13); also elsewhere on the board
/~IMU_CS: U32.8 (~Y7); also elsewhere on the board
/~INA239_CS: U32.3 (~Y2); also elsewhere on the board
/~IO_ADC_CS: U32.10 (~Y9); also elsewhere on the board
/~IO_DAC_CS: U32.5 (~Y4); also elsewhere on the board
/~IO_EXP_CS: U32.11 (~Y10); also elsewhere on the board
/~PG_15V: U1.37 (TXD0); also elsewhere on the board
/~PWR_INT: U1.39 (IO1); also elsewhere on the board
/~PWR_KILL: U1.18 (IO10); also elsewhere on the board
/~RS485_CS: U32.13 (~Y11); also elsewhere on the board
GND: C1.2, C13.2, C14.2, C39.2, C42.2, C63.2, C306.2, J1.A1 (GND), J1.A12 (GND), J1.B1 (GND), J1.B12 (GND), J1.SH (SHIELD), R19.1, R23.1, R24.1, R514.2, SW1.2, SW2.2, U1.1 (GND), U1.40 (GND), U1.41 (GND), U2.2 (GND), U32.12 (GND), U32.19 (~E1), U51.1 (NC), U51.3 (GND); also elsewhere on the board
unnamed: J1.A5 (CC1), R23.2
unnamed: J1.B5 (CC2), R24.2
unnamed: J1.A6 (D+), J1.B6 (D+), U2.1 (I/O1)
unnamed: J1.A7 (D-), J1.B7 (D-), U2.3 (I/O2)
unnamed: U1.14 (USB_D+), U2.6 (I/O1)
unnamed: U1.13 (USB_D-), U2.4 (I/O2)
SPI_MISO: U1.33 (IO40); also elsewhere on the board
SPI_MOSI: U1.34 (IO41); also elsewhere on the board
SPI_SCK: U1.35 (IO42); also elsewhere on the board

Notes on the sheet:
ESP32-S3 DECOUPLING CAPACITORS
USB-C PORT AND ESD PROTECTION
GPIO map follows include/config/pin_config.h
One output low at a time. E0 pull-up: all outputs high at reset.
RESET AND BOOT BUTTONS
SPI CHIP SELECT DECODER
Isolated 5 V, ISOW7841 output (purple)
Signals and grounds: default colour
74LV1T34GX DECOUPLING CAPACITOR
3.3 V rails (orange)
ADDRESS BIT D BUFFER
12 V input (yellow)
GPIO3 pull-up and GPIO45 pull-down are strap defaults. 74HC154 exposed pad: floating (datasheet).
POWER WIRE COLOURS (ATX SUPPLY CODE)
74LV1T34GX: VIH 1.37 V at 3.3 V.
+15 V and +16.5 V analog rails (dark red)
-15 V and -16.5 V analog rails (blue)
5 V rails and USB VBUS (red)
74HC154 DECOUPLING CAPACITOR
ESP32-S3-WROOM-2-N32R16V: 32 MB octal flash + 16 MB octal PSRAM (GPIO26-37 reserved by module)
GPIO47 is 1.8 V on N32R16V.
